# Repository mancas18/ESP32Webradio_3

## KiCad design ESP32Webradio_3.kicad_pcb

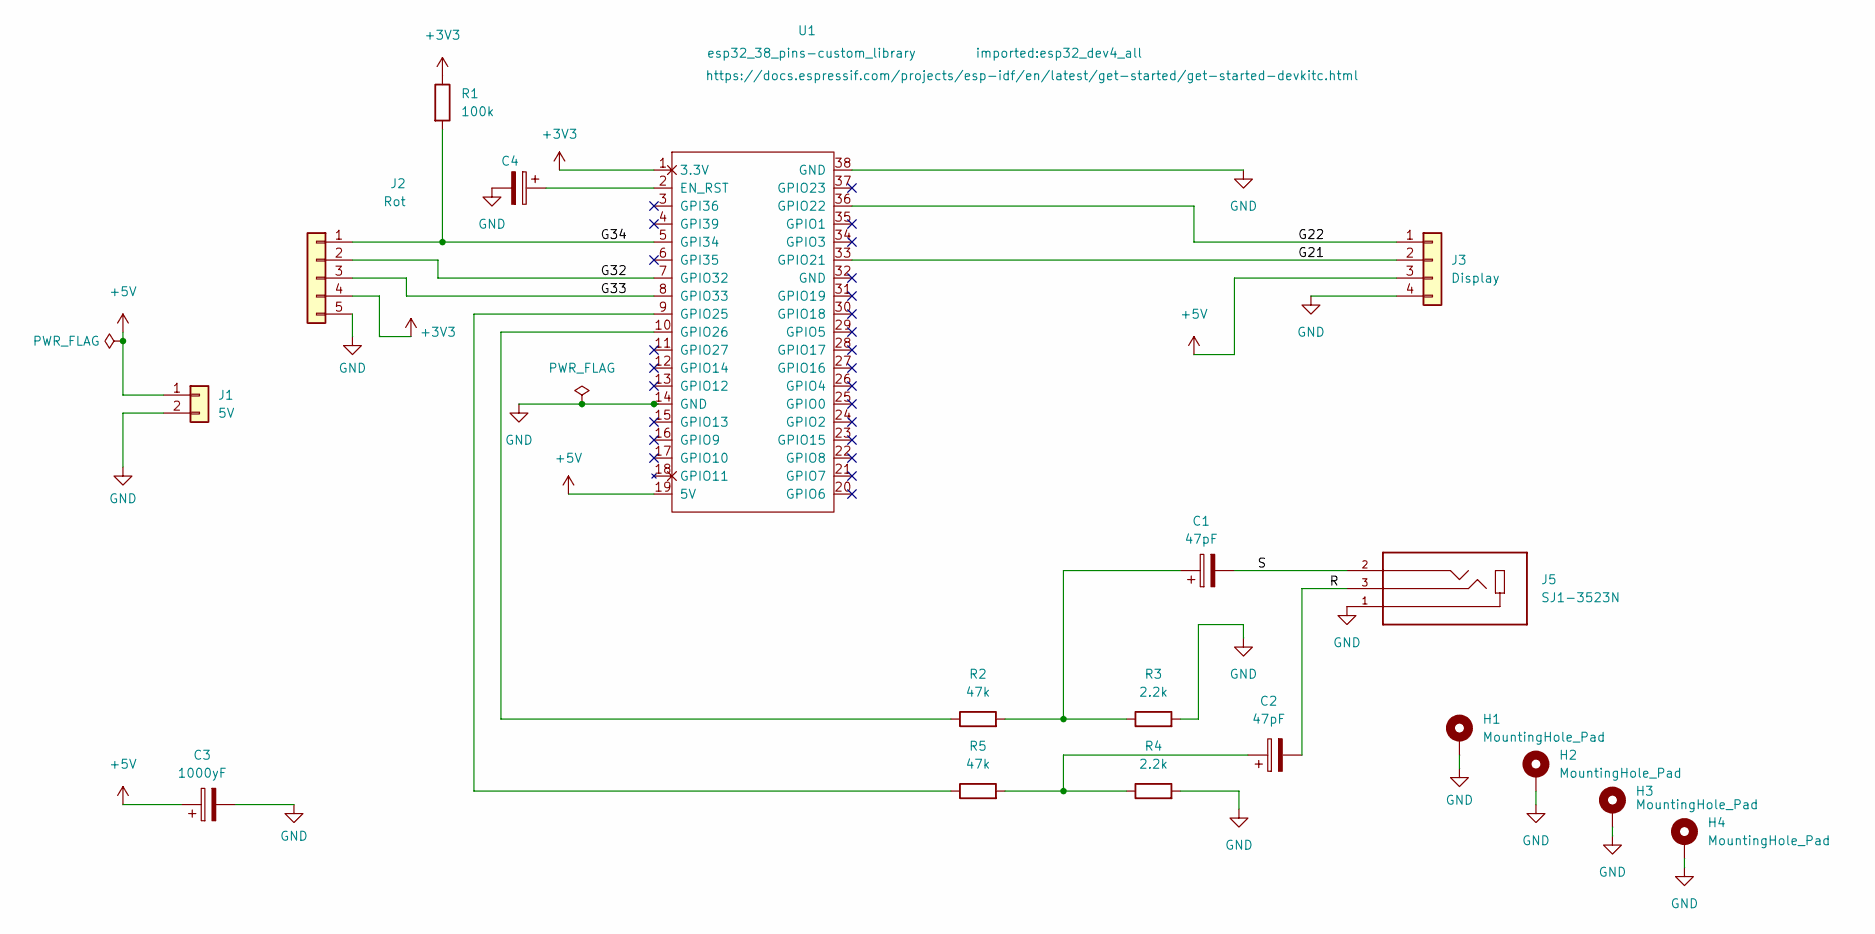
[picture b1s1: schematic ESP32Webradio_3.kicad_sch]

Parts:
C1, C2: 47pF; CP_Radial_D4.0mm_P2.00mm
C3: 1000yF; CP_Radial_D10.0mm_P2.50mm
C4: 10yF; CP_Radial_D4.0mm_P2.00mm
H1, H2, H3, H4: MountingHole_Pad; MountingHole_3.2mm_M3_DIN965_Pad
J1: 5V; PinHeader_1x02_P2.54mm_Vertical
J2: Rot; PinHeader_1x05_P2.54mm_Vertical
J3: Display; PinHeader_1x04_P2.54mm_Vertical
J5: SJ1-3523N; CUI_SJ1-3523N; PARTREV 1.02
R1: 100k; R_Axial_DIN0309_L9.0mm_D3.2mm_P2.54mm_Vertical
R2, R5: 47k; R_Axial_DIN0309_L9.0mm_D3.2mm_P2.54mm_Vertical
R3, R4: 2.2k; R_Axial_DIN0309_L9.0mm_D3.2mm_P2.54mm_Vertical
U1: esp32_38_pins-custom_library; esp32_dev4_all

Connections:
+3V3: J2.4, R1.1, U1.1 (3.3V)
+5V: C3.1, J1.1, J3.3, U1.19 (5V)
/G21: J3.2, U1.33 (GPIO21)
/G22: J3.1, U1.36 (GPIO22)
/G32: J2.2, U1.7 (GPIO32)
/G33: J2.3, U1.8 (GPIO33)
/G34: J2.1, R1.2, U1.5 (GPI34)
/R: C2.2, J5.3
/S: C1.2, J5.2
GND: C3.2, C4.2, H1.1, H2.1, H3.1, H4.1, J1.2, J2.5, J3.4, J5.1, R3.2, R4.2, U1.14 (GND), U1.38 (GND)
unnamed: C1.1, R2.2, R3.1
unnamed: C2.1, R4.1, R5.2
unnamed: C4.1, U1.2 (EN_RST)
unnamed: R2.1, U1.10 (GPIO26)
unnamed: R5.1, U1.9 (GPIO25)

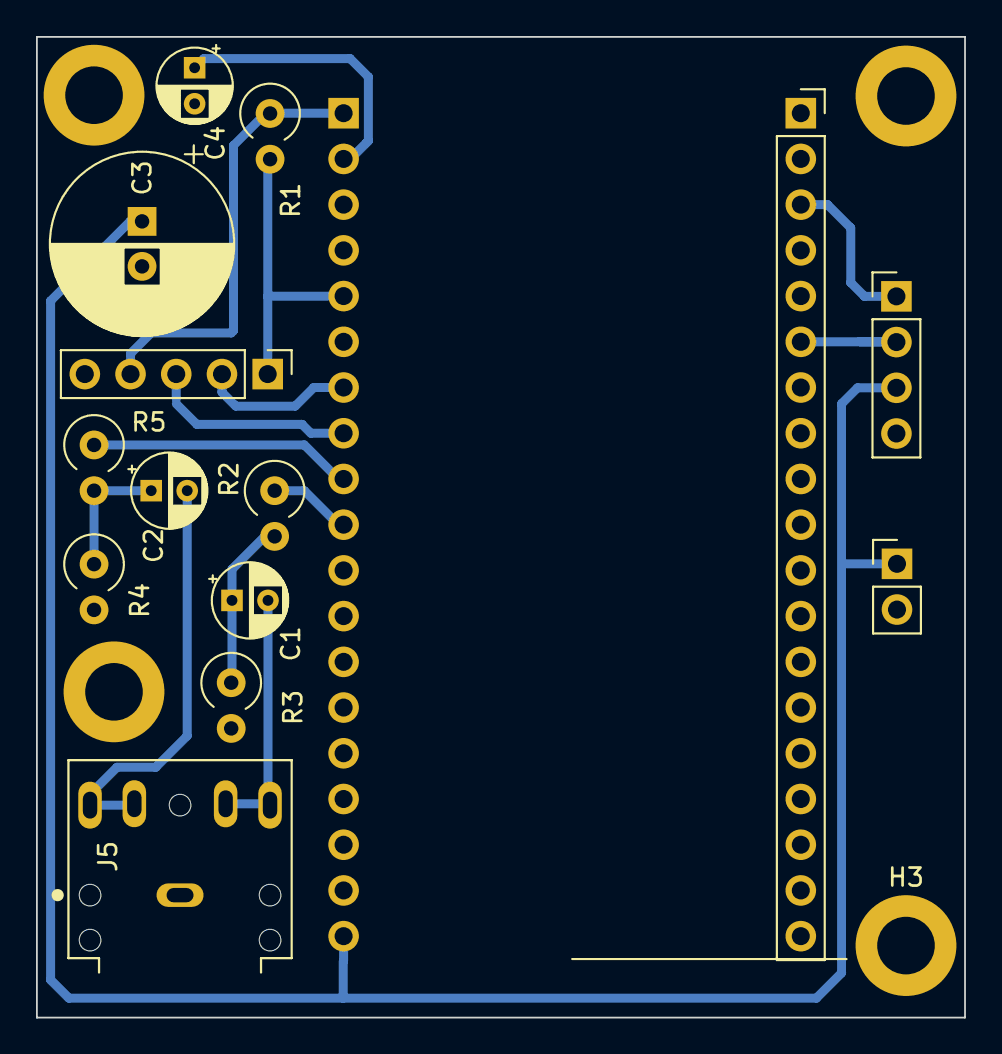
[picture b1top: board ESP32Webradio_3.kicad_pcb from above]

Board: 2 copper layers, 51.6 x 54.5 mm, 18 parts (0 on the bottom side), 15 nets.

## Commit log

2022-05-27 initial upload
2022-06-10 flash witout button capacitor added
2022-06-10 clear circuits
